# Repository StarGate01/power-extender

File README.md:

# Power Extender

Hardware and software for a power and IO extension PCB with current monitoring and I2C interface.

This project has been generously supported by [PCBWay](https://www.pcbway.com/). Read more about this project and also my review of the manufacturing on my blog: [Design And Assembly Of An I2C Relay PCB](https://chrz.de/2021/07/16/design-and-assembly-of-an-i2c-relay-pcb/)

## Usage

Use [KiCad](https://www.kicad.org/) with my [CustomComponents](https://github.com/StarGate01/KiCadLibs) library to view and edit the hardware project, or download the [fabrication files](fabrication) for PCB and/or PCBA manufacturing. I used [KiBOM](https://github.com/SchrodingersGat/kibom) to generate the BOM. You can also download the complete [schematics as PDF](hardware/power-extender_schematics_rev1_1.pdf).

See the [Arduino library documentation](https://github.com/StarGate01/power-extender/tree/master/software/power-extender-arduino/lib/power-extender) for usage with the Arduino framework. The library is also available on [PlatformIO](https://platformio.org/lib/show/12563/power-extender). Use [Visual Studio Code](https://code.visualstudio.com/) and the [PlatformIO](https://platformio.org/) plugin to edit the Arduino library and tests.

See the [Raspberry Pi library documentation](https://github.com/StarGate01/power-extender/tree/master/software/power-extender-raspberrypi) for usage with the Raspberry Pi Python 3 `smbus` framework.

## Features and Specifications

- Power input via `5V` and `3V3` pins
  - Min. `250mA @ 5V` to actuate all four relays simultaneously
  - Less than `30mA @ 5V` standby current
  - `3V3` voltage level is only required for I2C level shifting if the I2C signal level is `3.3V` instead of `5V`
- I2C bus for connection to a I2C master via JST header `RPI`
  - I2C bus passthrough via JST header `PASS`
  - Internal pullup resistors
  - Level-shifting `3.3V - 5V` tolerant bus
- Four `SRD-05VDC-SL-C` three-lead (`NC - COM - NO`) magnetic relays
  - Each has a `CC6902SO-10A` inductive current measuring IC connected across `COM`
  - Galvanically isolated driver circuit using an optocoupler
  - Flyback diode protection
  - Red status LED indicates `COM - NO` actuation
  - `2oz` thick copper traces enable high currents
  - Isolation milling reduces risk of shorting in damp environments
  - Maximum power: `10A, 250VAC, 110VDC`
  - Contact load rating: resistive `7A @ 28VDC`, `10A @ 125VAC`, `7A @ 240VAC`, inductive `3A @ 120VAC`, `3A @ 28VDC`
- One `PCA9557` 8-channel GPIO port (I2C address: `0x18`), logic level `0V | 5V`
  - GPIO channels `0Z` - `3` connected to JST header `DIGITAL`
  - Relays are connected to GPIO channels `4` - `7`
  - Maximum current (except channel `0Z`): `25mA` sink, `20mA` source per channel, max. total: `100mA` sink, `85mA` source
  - Channel `0Z` is high-impedance and open-drain (see datasheet for details)
- Two `ADS1115` 4-channel 16-bit ADC ports, voltage range `0V - 5V`
  - All four pins of ADC 1 connected to current measuring ICs (I2C address: `0x48`)
  - All four pins of ADC 2 connected to JST header `ANALOG` (I2C address: `0x49`)
  - Configurable sample rate and gain amplifier
  - Max. `10mA` continuous input current

For further specifications and ratings, all [datasheets](https://github.com/StarGate01/power-extender/tree/master/datasheets) can be found in this repository.

### Sensor Calibration

Due to the inherent nature of magnetic relays, the inductive current measuring ICs and also the ADCs experience a measurement offset while the relays are energized. It is recommended to measure the actual load at a distance from the board, in order to obtain reference values. These reference values should then be used to compute an offset or function for each channel and amount of relays energized. 

For no load (floating) using an Arduino Uno, the maximum absolute measurement offset was found to be about as follows.

| Amount of relays energized | Offset at energized channel | Offset at disabled channel |
| -------------------------- | --------------------------- | -------------------------- |
| 0                          | `0.05A`                     | `0.05A`                    |
| 1                          | `1A`                        | `0.7A`                     |
| 2                          | `1.5A`                      | `1.3A`                     |
| 3                          | `2A`                        | `1.8A`                     |
| 4                          | `2.4A`                      | N / A                      |

Please note that these offsets are dependent on load and environmental factors.

## PCB Details

**17 unique** parts, **60 SMT** parts, **12 THT** parts on a double-sided `90mm x 71mm` PCB with `2oz` copper finish.

Component cost per board: about `$25` (Ignoring shipping, bulk discounts and changes in price over time).

<details>
<summary>BOM</summary>

|Item #|Designator                            |Quantity|Manufacturer          |Manufacturer Part #  |Description / Value                         |Distributor|Distributor part #|Package / Footprint|Type|Notes|
|------|--------------------------------------|--------|----------------------|---------------------|--------------------------------------------|-----------|------------------|-------------------|----|-----|
|1     |C11, C21, C31, C41                    |4       |Any                   |TBD                  |CAP CER 100PF MAX. 5% MIN. 10V 0805 SMD     |Any        |TBD               |SMD 0805           |SMD |     |
|2     |C1, C2, C12, C22, C32, C42            |6       |Any                   |TBD                  |CAP CER 100NF MAX. 5% MIN. 10V 0805 SMD     |Any        |TBD               |SMD 0805           |SMD |     |
|3     |D12, D22, D32, D42                    |4       |Shikues               |1N4007F              |DIODE 1N4007 SMAF                           |LCSC       |C110856           |SMAF               |SMD |     |
|4     |D11, D21, D31, D41                    |4       |Everlight Elec        |17-21SURC/S530-A3/TR8|LED RED 2V 0805 SMD                         |LCSC       |C72037            |SMD 0805           |SMD |     |
|5     |J1, J2, J3, J4                        |4       |Any                   |TBD                  |CONN JST-XH PITCH-2.50MM VERTICAL MALE 5 PIN|Any        |TBD               |Through Hole       |PTH |     |
|6     |J11, J21, J31, J41                    |4       |Ningbo Kangnex Elec   |WJ128V-5.0-3P        |CONN SCREW TERMINAL PITCH-5.0MM 3 PIN 20A   |LCSC       |C8270             |Through Hole       |PTH |     |
|7     |K11, K21, K31, K41                    |4       |Ningbo Songle Relay   |SRD-05VDC-SL-C       |RELAY SEALED SENSITIVE 5V 10A               |LCSC       |C35449            |Through Hole       |PTH |     |
|8     |Q1, Q2                                |2       |Shikues               |BSS138               |MOSFET N-CH SOT-23-3                        |LCSC       |C112239           |SOT-23-3           |SMD |     |
|9     |Q11, Q21, Q31, Q41                    |4       |Nexperia              |PMBT3904,215         |BJT NPN SOT-23-3                            |LCSC       |C8667             |SOT-23-3           |SMD |     |
|10    |R14, R24, R34, R44                    |4       |Any                   |TBD                  |RES 100 OHM MAX. 1% MIN. 1/8W 0805 SMD      |Any        |TBD               |SMD 0805           |SMD |     |
|11    |R11, R12, R21, R22, R31, R32, R41, R42|8       |Any                   |TBD                  |RES 200 OHM MAX. 1% MIN. 1/8W 0805 SMD      |Any        |TBD               |SMD 0805           |SMD |     |
|12    |R1, R13, R23, R33, R43                |5       |Any                   |TBD                  |RES 1K OHM MAX. 1% MIN. 1/8W 0805 SMD       |Any        |TBD               |SMD 0805           |SMD |     |
|13    |R2, R3, R4, R5, R15, R25, R35, R45    |8       |Any                   |TBD                  |RES 10K OHM MAX. 1% MIN. 1/8W 0805 SMD      |Any        |TBD               |SMD 0805           |SMD |     |
|14    |U1, U3                                |2       |Texas Instruments     |ADS1115IDGSR         |IC I2C 4 CH ADC VSSOP-10                    |LCSC       |C37593            |VSSOP-10           |SMD |     |
|15    |U12, U22, U32, U42                    |4       |Cross Chip            |CC6902SO-10A         |IC CURRENT SENSOR 5V 10A SOP-8              |LCSC       |C350865           |SOP-8              |SMD |     |
|16    |U11, U21, U31, U41                    |4       |Sharp Microelectronics|PC817X2CSP9F         |IC OPTOCOUPLER SMD-4                        |LCSC       |C66405            |SMD-4              |SMD |     |
|17    |U2                                    |1       |NXP Semicon           |PCA9557PW,118        |IC I2C 8 CH IO EXPANDER TSSOP-16            |LCSC       |C141380           |TSSOP-16           |SMD |     |

</details>

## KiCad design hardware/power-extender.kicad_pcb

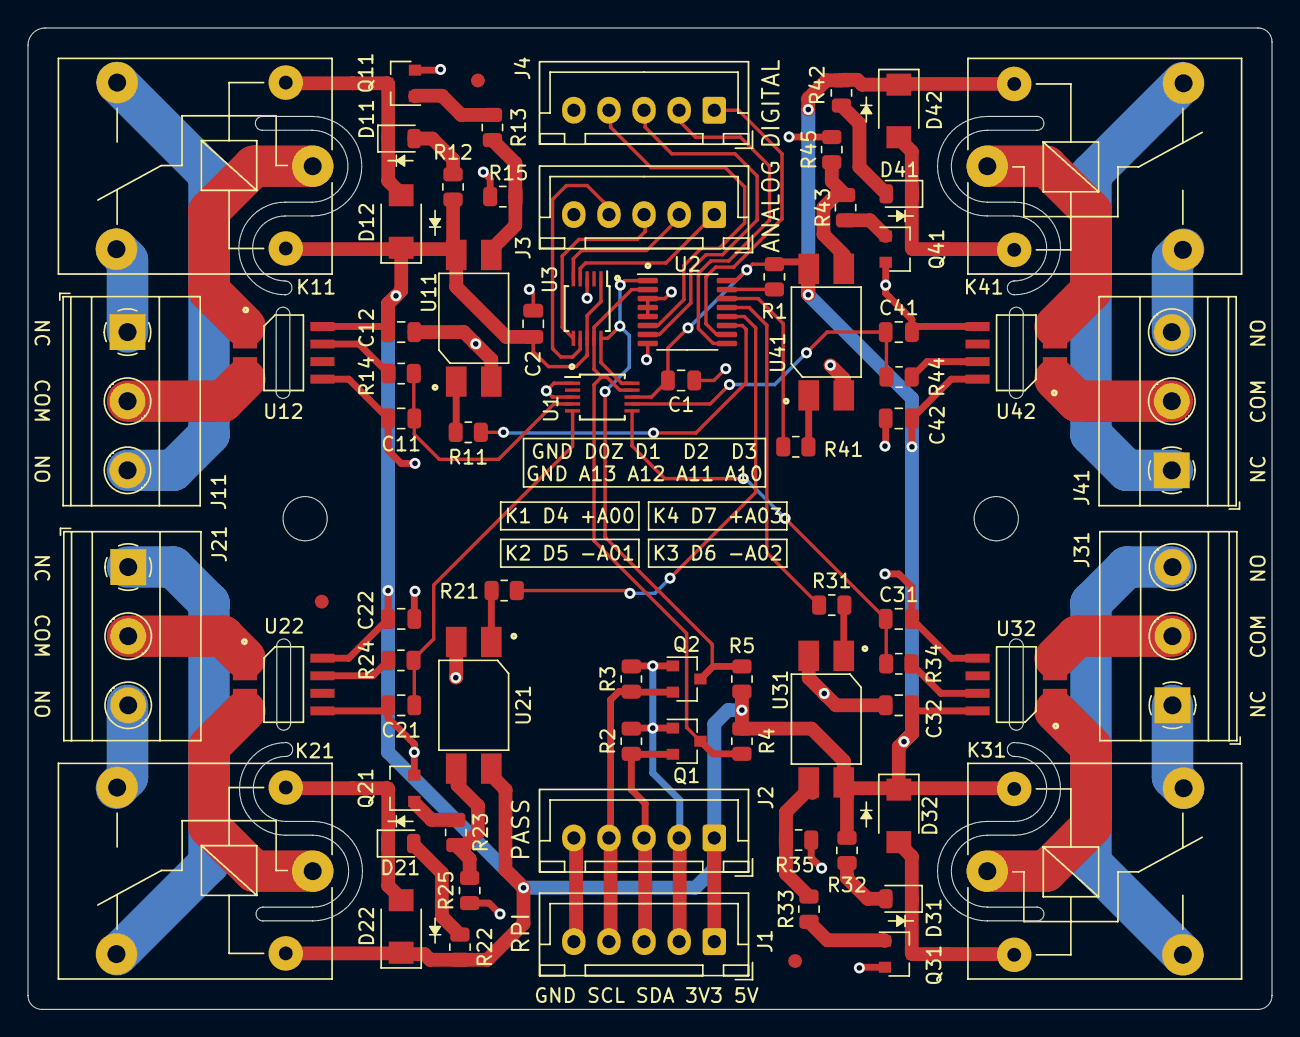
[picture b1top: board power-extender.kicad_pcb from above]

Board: 2 copper layers, 90.0 x 71.0 mm, 77 parts (0 on the bottom side), 64 nets.

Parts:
C1, C2, C12, C22, C32, C42: 100N; C_0805_2012Metric
C11, C21, C31, C41: 100P; C_0805_2012Metric
D11, D21, D31, D41: LED; LED_0805_2012Metric
D12, D22, D32, D42: 1N4007F; D_SMAF
FID1, FID2, FID3: Fiducial; Fiducial_1mm_Mask2mm
H1, H2: MountingHole; MountingHole_3.2mm_M3
J1: IFACE RPI; JST_XH_B5B-XH-A_1x05_P2.54mm_Vertical
J2: IFACE PASS; JST_XH_B5B-XH-A_1x05_P2.54mm_Vertical
J3: AUX ANALOG; JST_XH_B5B-XH-A_1x05_P2.54mm_Vertical
J4: AUX DIGITAL; JST_XH_B5B-XH-A_1x05_P2.54mm_Vertical
J11, J21, J31, J41: LOAD; TerminalBlock_Phoenix_MKDS-1,5-3_1x03_P5.00mm_Horizontal
K11, K21, K31, K41: SRD-05VDC-SL-C; Relay_SPDT_SANYOU_SRD_Series_Form_C
Q1, Q2: BSS138; SOT-23
Q11, Q21, Q31, Q41: PMBT3904; SOT-23
R1, R13, R23, R33, R43: 1K; R_0805_2012Metric
R2, R3, R4, R5, R15, R25, R35, R45: 10K; R_0805_2012Metric
R11, R12, R21, R22, R31, R32, R41, R42: 200R; R_0805_2012Metric
R14, R24, R34, R44: 100R; R_0805_2012Metric
U1, U3: ADS1115IDGS; TSSOP-10_3x3mm_P0.5mm
U2: PCA9557PW; TSSOP-16_4.4x5mm_P0.65mm
U11, U21, U31, U41: PC817X2CSP9F
U12, U22, U32, U42: CC6902SO-10A; CC690XSO-XA

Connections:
+3V3: J1.2, J2.2, Q1.1, Q2.1, R2.1, R3.1
+5V: C1.1, C2.1, C12.1, C22.1, C32.1, C42.1, D12.1, D22.1, D32.1, D42.1, J1.1, J2.1, K11.5, K21.5, K31.5, K41.5, R1.1, R4.1, R5.1, R12.1, R22.1, R32.1, R42.1, U1.8, U2.16, U3.1, U3.8, U11.4, U12.8, U21.4, U22.8, U31.4, U32.8, U41.4, U42.8
/Relay-A/TRIGGER: R11.1, U2.11
/Relay-A/VIOUT: C11.1, R14.1, U1.4
/Relay-B/TRIGGER: R21.1, U2.12
/Relay-B/VIOUT: C21.1, R24.1, U1.5
/Relay-C/TRIGGER: R31.1, U2.13
/Relay-C/VIOUT: C31.1, R34.1, U1.6
/Relay-D/TRIGGER: R41.1, U2.14
/Relay-D/VIOUT: C41.1, R44.1, U1.7
A0: J3.1, U3.4
A1: J3.2, U3.5
A2: J3.3, U3.6
A3: J3.4, U3.7
D0Z: J4.4, U2.6
D1: J4.3, U2.7
D2: J4.2, U2.9
D3: J4.1, U2.10
GND: C1.2, C2.2, C11.2, C12.2, C21.2, C22.2, C31.2, C32.2, C41.2, C42.2, J1.5, J2.5, J3.5, J4.5, Q11.2, Q21.2, Q31.2, Q41.2, R15.2, R25.2, R35.2, R45.2, U1.1, U1.3, U2.3, U2.4, U2.5, U2.8, U3.3, U11.2, U12.5, U21.2, U22.5, U31.2, U32.5, U41.2, U42.5
unnamed: D11.1, D12.2, K11.2, Q11.3
unnamed: D11.2, R12.2
unnamed: D21.1, D22.2, K21.2, Q21.3
unnamed: D21.2, R22.2
unnamed: D31.1, D32.2, K31.2, Q31.3
unnamed: D31.2, R32.2
unnamed: D41.1, D42.2, K41.2, Q41.3
unnamed: D41.2, R42.2
unnamed: J11.1, K11.4
unnamed: J11.2, U12.3, U12.4
unnamed: J11.3, K11.3
unnamed: J21.1, K21.4
unnamed: J21.2, U22.1, U22.2
unnamed: J21.3, K21.3
unnamed: J31.1, K31.4
unnamed: J31.2, U32.3, U32.4
unnamed: J31.3, K31.3
unnamed: J41.1, K41.4
unnamed: J41.2, U42.1, U42.2
unnamed: J41.3, K41.3
unnamed: K11.1, U12.1, U12.2
unnamed: K21.1, U22.3, U22.4
unnamed: K31.1, U32.1, U32.2
unnamed: K41.1, U42.3, U42.4
unnamed: Q11.1, R13.2
unnamed: Q21.1, R23.2
unnamed: Q31.1, R33.2
unnamed: Q41.1, R43.2
unnamed: R1.2, U2.15
unnamed: R11.2, U11.1
unnamed: R13.1, R15.1, U11.3
unnamed: R14.2, U12.7
unnamed: R21.2, U21.1
unnamed: R23.1, R25.1, U21.3
unnamed: R24.2, U22.7
unnamed: R31.2, U31.1
unnamed: R33.1, R35.1, U31.3
unnamed: R34.2, U32.7
unnamed: R41.2, U41.1
unnamed: R43.1, R45.1, U41.3
unnamed: R44.2, U42.7
SCL3V3: J1.4, J2.4, Q2.2, R3.2
SCL5V: Q2.3, R5.2, U1.10, U2.1, U3.10
SDA3V3: J1.3, J2.3, Q1.2, R2.2
SDA5V: Q1.3, R4.2, U1.9, U2.2, U3.9

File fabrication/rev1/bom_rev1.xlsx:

Item # | Designator | Quantity | Manufacturer | Manufacturer Part # | Description / Value | Distributor | Distributor part # | Package / Footprint | Type | Notes
1 | C11, C21, C31, C41 | 4 | Any | TBD | CAP CER 100PF MAX. 5% MIN. 10V 0805 SMD | Any | TBD | SMD 0805 | SMD
2 | C1, C2, C12, C22, C32, C42 | 6 | Any | TBD | CAP CER 100NF MAX. 5% MIN. 10V 0805 SMD | Any | TBD | SMD 0805 | SMD
3 | D12, D22, D32, D42 | 4 | Shikues | 1N4007F | DIODE 1N4007 SMAF | LCSC | C110856 | SMAF | SMD
4 | D11, D21, D31, D41 | 4 | Everlight Elec | 17-21SURC/S530-A3/TR8 | LED RED 2V 0805 SMD | LCSC | C72037 | SMD 0805 | SMD
5 | J1, J2, J3, J4 | 4 | Any | TBD | CONN JST-XH PITCH-2.50MM VERTICAL MALE 5 PIN | Any | TBD | Through Hole | THT
6 | J11, J21, J31, J41 | 4 | Ningbo Kangnex Elec | WJ128V-5.0-3P | CONN SCREW TERMINAL PITCH-5.0MM 3 PIN 20A | LCSC | C8270 | Through Hole | THT
7 | K11, K21, K31, K41 | 4 | Ningbo Songle Relay | SRD-05VDC-SL-C | RELAY SEALED SENSITIVE 5V 10A | LCSC | C35449 | Through Hole | THT
8 | Q1, Q2 | 2 | Shikues | BSS138 | MOSFET N-CH SOT-23-3 | LCSC | C112239 | SOT-23-3 | SMD
9 | Q11, Q21, Q31, Q41 | 4 | Nexperia | PMBT3904,215 | BJT NPN SOT-23-3 | LCSC | C8667 | SOT-23-3 | SMD
10 | R14, R24, R34, R44 | 4 | Any | TBD | RES 100 OHM MAX. 1% MIN. 1/8W 0805 SMD | Any | TBD | SMD 0805 | SMD
11 | R11, R12, R21, R22, R31, R32, R41, R42 | 8 | Any | TBD | RES 200 OHM MAX. 1% MIN. 1/8W 0805 SMD | Any | TBD | SMD 0805 | SMD
12 | R1, R13, R23, R33, R43 | 5 | Any | TBD | RES 1K OHM MAX. 1% MIN. 1/8W 0805 SMD | Any | TBD | SMD 0805 | SMD
13 | R2, R3, R4, R5, R15, R25, R35, R45 | 8 | Any | TBD | RES 10K OHM MAX. 1% MIN. 1/8W 0805 SMD | Any | TBD | SMD 0805 | SMD
14 | U1, U3 | 2 | Texas Instruments | ADS1115IDGSR | IC I2C 4 CH ADC VSSOP-10 | LCSC | C37593 | VSSOP-10 | SMD
15 | U12, U22, U32, U42 | 4 | Cross Chip | CC6902SO-10A | IC CURRENT SENSOR 5V 10A SOP-8 | LCSC | C350865 | SOP-8 | SMD
16 | U11, U21, U31, U41 | 4 | Sharp Microelectronics | PC817X2CSP9F | IC OPTOCOUPLER SMD-4 | LCSC | C66405 | SMD-4 | SMD
17 | U2 | 1 | NXP Semicon | PCA9557PW,118 | IC I2C 8 CH IO EXPANDER TSSOP-16 | LCSC | C141380 | TSSOP-16 | SMD

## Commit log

2021-06-11 Add design goals
2021-06-13 First version of relays and measurement circuits
2021-06-14 First draft
2021-06-14 Firnish schematic first version
2021-06-15 checkpoint commit
2021-06-16 relay layout checkpoint
2021-06-16 traces done
2021-06-16 first verion of layout done
2021-06-16 Cleanup
2021-06-16 Add images
2021-06-17 Add bjt pulldown, prepare for export
2021-06-18 rev1 final touchups
2021-06-18 Submit rev1
2021-06-18 fix readme
2021-06-18 save file
2021-06-21 Add rev 1.1 fabrication files
2021-07-10 progress
2021-07-15 Begin implementing arduino library
2021-07-16 Add missing datasheets
2021-07-16 Add specs to readme
2021-07-16 Add arduino library
2021-07-16 Clarify docs and test aux GPIO
2021-07-16 Add photo
2021-07-16 Add pdf schematics
2021-07-16 fix links
2021-07-20 Add raspberry pi python library
2021-07-20 Add raspi lib docs
2021-07-20 typo
2022-05-26 Fix pio library file
2022-05-26 fix cubecell board incompatibilities
